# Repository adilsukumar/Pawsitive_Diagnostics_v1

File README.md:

# Pawsitive Diagnostics v1

An early-stage animal-health monitoring prototype that connects wearable-sensor concepts, a mobile-first dashboard, cloud data flow, and experimental machine-learning modules.

Pawsitive Diagnostics is being developed as a student startup by an interdisciplinary team. I lead the software and startup tracks: backend and cloud architecture, model experimentation, hardware-to-application integration, technical planning, team coordination, pitch development, and exploration of funding and intellectual-property pathways.

> **Research prototype:** This software is not a veterinary medical device. Its scores and classifications have not been clinically validated and must not be used to diagnose or treat an animal.

## What is in this repository

- **React/TypeScript application** for pet profiles, sensor dashboards, reports, maps, and owner-facing interactions
- **FastAPI prototype** defining interfaces for audio, image, motion, environmental, and combined-health analyses
- **Experimental ML modules** for feature extraction, anomaly detection, clustering, and multimodal score aggregation
- **Supabase integration** for application data
- **Hardware design files** including PCB schematics, fabrication outputs, and component documentation
- **Capacitor configuration** for packaging the web application for mobile platforms

## System view

```text
Wearable sensors / media
          |
          v
  ESP32 and telemetry layer
          |
          v
Cloud storage and FastAPI interfaces
          |
          v
Experimental signal / ML modules
          |
          v
React dashboard and shareable reports
```

The repository brings these layers together so that changes to a sensor or model can be traced through the backend and into the user interface. Some screens and API responses still use simulated data while hardware integration and dataset collection continue.

## Experimental analysis modules

| Module | Current engineering direction |
| --- | --- |
| BarkSense | Acoustic features and prototype vocalisation classification |
| SkinSense | Image-processing and transfer-learning experiments |
| MotionSense | IMU feature extraction and gait/activity analysis |
| LocationSense | Spatial clustering and safe-zone logic |
| TemperatureSense | Thermal trend and anomaly analysis |
| VitalSense | Filtering and peak detection for physiological signals |
| PressureSense | Barometric trend analysis |
| LightSense | Light/UV exposure estimation |
| CombineSense | Experimental aggregation of multiple signals |

These modules are engineering experiments. Model architecture files do not imply that a model is trained, calibrated, or ready for deployment; performance must be established on representative labelled datasets.

## Technology

React · TypeScript · Vite · Tailwind CSS · FastAPI · Python · PyTorch/TensorFlow experiments · Supabase · AWS · Docker · ESP32 · Capacitor

## Run the web application

### Prerequisites

- Node.js 18+
- npm

```bash
git clone https://github.com/AdilSukumar/Pawsitive_Diagnostics_v1.git
cd Pawsitive_Diagnostics_v1
npm install
cp .env.example .env
npm run dev
```

Review `.env.example` before enabling external services. Never commit API keys.

## Run the ML/API prototype

```bash
cd ml_backend
python -m venv .venv
# Windows: .venv\Scripts\activate
# macOS/Linux: source .venv/bin/activate
pip install -r requirements.txt
uvicorn api.main:app --reload
```

## Validation status and next steps

- Replace simulated API outputs with versioned model artefacts.
- Build a consented, labelled dataset with veterinary guidance.
- Define subject-level train/validation/test splits and report uncertainty.
- Validate sensor reliability against reference instruments.
- Add integration tests from telemetry ingestion through report generation.
- Conduct usability and safety reviews before any real-world health use.

## Team and recognition

The project has been presented at national student innovation events, including a nationwide second-place ideathon result and a top-six national hackathon finish. The team is preparing an intellectual-property application and exploring institutional support. These milestones reflect product development; they are not evidence of clinical efficacy.

## License

See [LICENSE](LICENSE).

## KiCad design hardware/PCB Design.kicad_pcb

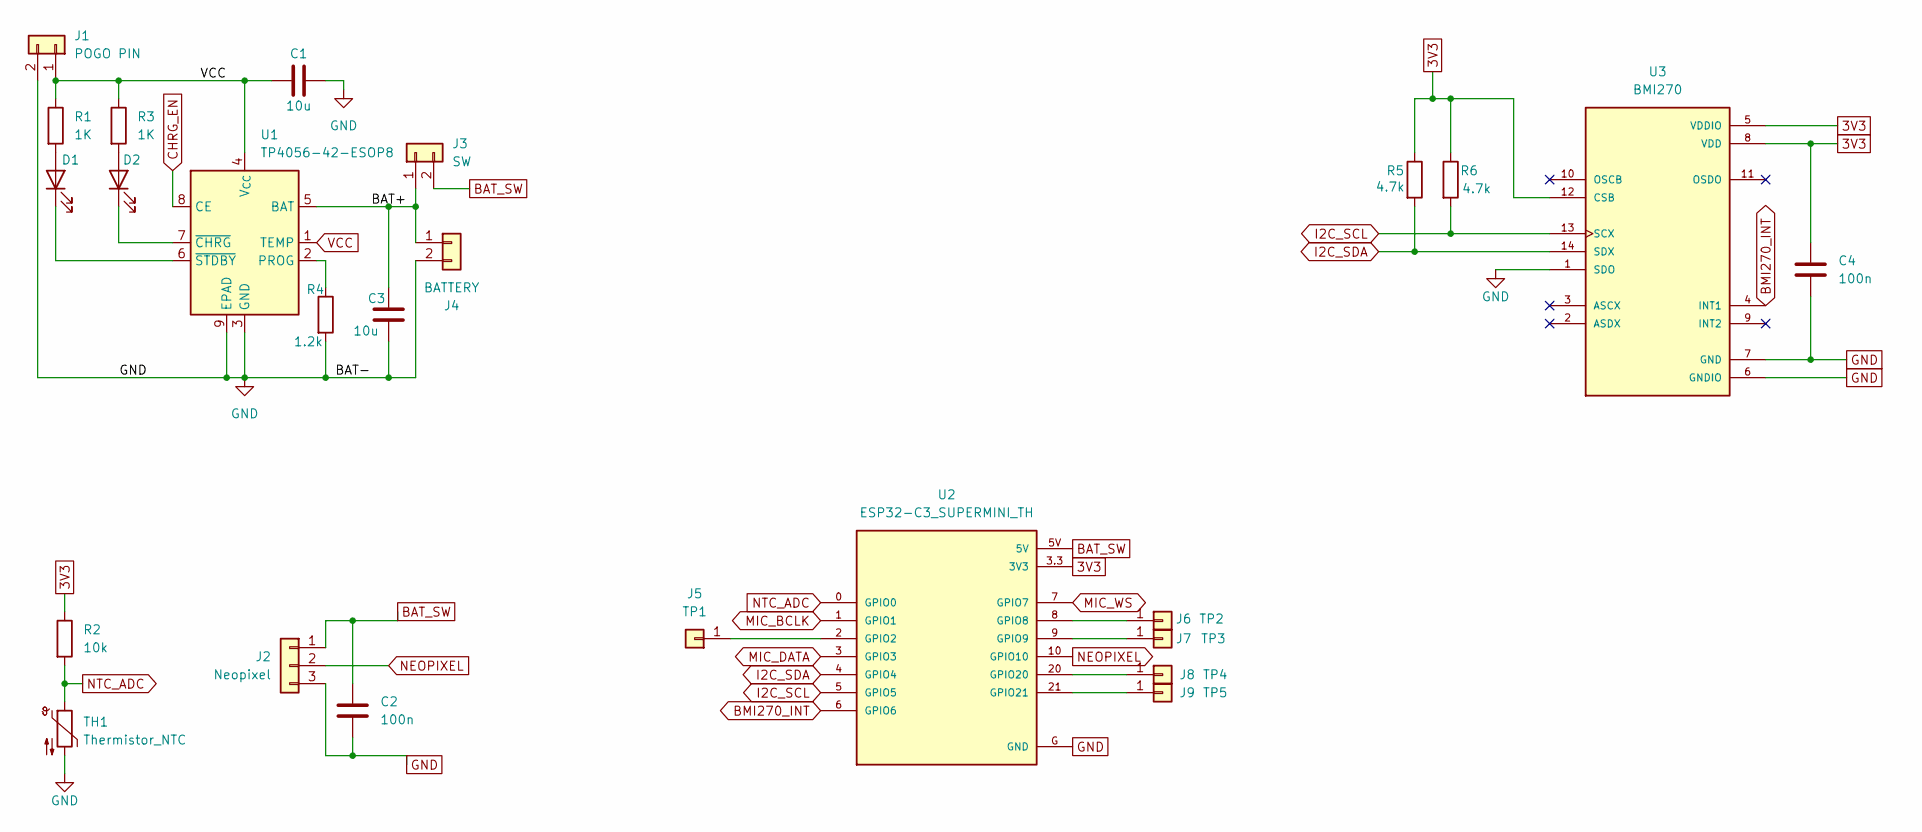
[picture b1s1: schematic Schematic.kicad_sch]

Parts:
C1, C3: 10u; C_0805_2012Metric
C2, C4: 100n; C_0603_1608Metric_Pad1.08x0.95mm_HandSolder
D1, D2: LED; LED_D3.0mm
J1: POGO PIN; JST_EH_B2B-EH-A_1x02_P2.50mm_Vertical
J2: Neopixel; JST_PH_B3B-PH-K_1x03_P2.00mm_Vertical
J3: SW; PinHeader_1x02_P1.00mm_Vertical
J4: BATTERY; JST_EH_B2B-EH-A_1x02_P2.50mm_Vertical
J5: TP1; PinHeader_1x01_P2.54mm_Vertical
J6: TP2; PinHeader_1x01_P2.54mm_Vertical
J7: TP3; PinHeader_1x01_P2.54mm_Vertical
J8: TP4; PinHeader_1x01_P2.54mm_Vertical
J9: TP5; PinHeader_1x01_P2.54mm_Vertical
R1, R3: 1K; R_0603_1608Metric
R2: 10k; R_0603_1608Metric
R4: 1.2k; R_0603_1608Metric
R5, R6: 4.7k; R_0603_1608Metric
TH1: Thermistor_NTC; RV_Disc_D12mm_W4.2mm_P7.5mm
U1: TP4056-42-ESOP8; SOIC-8-1EP_3.9x4.9mm_P1.27mm_EP2.41x3.3mm_ThermalVias
U2: ESP32-C3_SUPERMINI_TH; MODULE_ESP32-C3_SUPERMINI_TH
U3: BMI270; XDCR_BMI270

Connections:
3V3: C4.1, R2.1, R5.1, R6.1, U2.3.3 (3V3), U3.5 (VDDIO), U3.8 (VDD), U3.12 (CSB)
/BAT+: C3.2, J3.1, J4.1, U1.5 (BAT)
BAT_SW: C2.1, J2.1, J3.2, U2.5V
BMI270_INT: U2.6 (GPIO6), U3.4 (INT1)
CHRG_EN: U1.8 (CE)
GND: C1.2, C2.2, C3.1, C4.2, J1.2, J2.3, J4.2, R4.2, TH1.2, U1.3 (GND), U1.9 (EPAD), U2.G (GND), U3.1 (SDO), U3.6 (GNDIO), U3.7 (GND)
I2C_SCL: R6.2, U2.5 (GPIO5), U3.13 (SCX)
I2C_SDA: R5.2, U2.4 (GPIO4), U3.14 (SDX)
MIC_BCLK: U2.1 (GPIO1)
MIC_DATA: U2.3 (GPIO3)
MIC_WS: U2.7 (GPIO7)
NEOPIXEL: J2.2, U2.10 (GPIO10)
NTC_ADC: R2.2, TH1.1, U2.0 (GPIO0)
unnamed: D1.2 (A), R1.2
unnamed: D1.1 (K), U1.6 (~STDBY)
unnamed: D2.2 (A), R3.2
unnamed: D2.1 (K), U1.7 (~CHRG)
unnamed: J5.1 (Pin_1_1), U2.2 (GPIO2)
unnamed: J6.1 (Pin_1_1), U2.8 (GPIO8)
unnamed: J7.1 (Pin_1_1), U2.9 (GPIO9)
unnamed: J8.1 (Pin_1_1), U2.20 (GPIO20)
unnamed: J9.1 (Pin_1_1), U2.21 (GPIO21)
unnamed: R4.1, U1.2 (PROG)
VCC: C1.1, J1.1, R1.1, R3.1, U1.1 (TEMP), U1.4 (V_{CC})

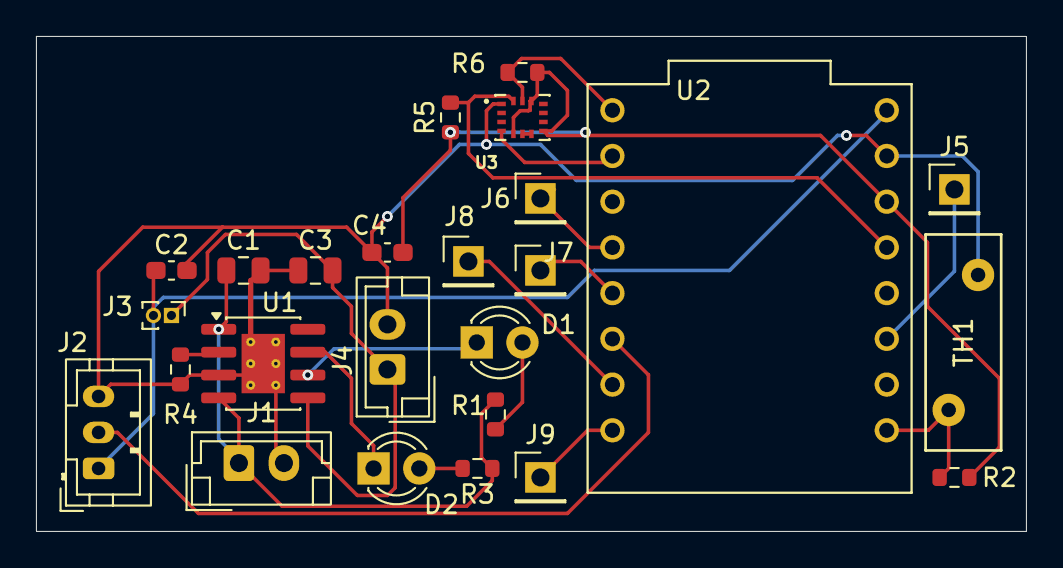
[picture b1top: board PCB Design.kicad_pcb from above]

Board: 2 copper layers, 55.0 x 27.5 mm, 25 parts (0 on the bottom side), 20 nets.

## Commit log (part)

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2026-06-15 Added PCB Design and Schematic
2026-06-15 Added gerber files of the PCB for manufacturing
2026-06-15 feat: premium UI/UX overhaul, 9 Sense AI modules, and mock ML backend
